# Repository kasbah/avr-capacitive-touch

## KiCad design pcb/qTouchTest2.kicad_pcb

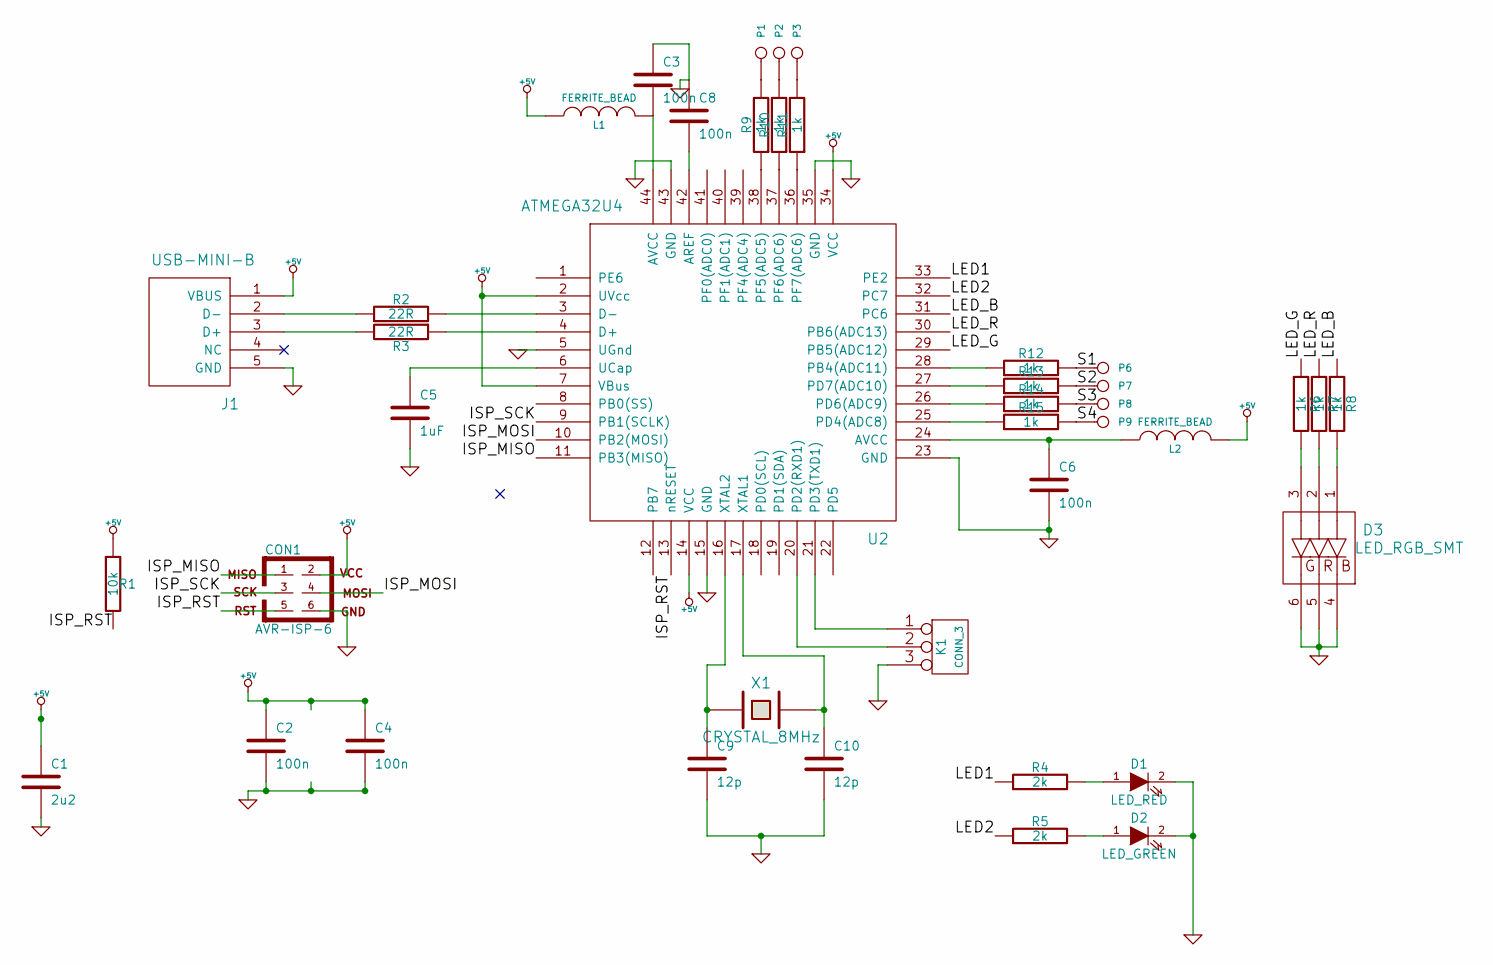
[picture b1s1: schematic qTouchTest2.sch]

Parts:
C1: 2u2
C2, C3, C4, C6, C8: 100n
C5: 1uF
C9, C10: 12p
CON1: AVR-ISP-6
D1: LED_RED
D2: LED_GREEN
D3: LED_RGB_SMT
J1: USB-MINI-B
K1: CONN_3
L1, L2: FERRITE_BEAD
P1, P2, P3, P6, P7, P8, P9: CONN_1
R1: 10k
R2, R3: 22R
R4, R5: 2k
R6, R7, R8, R9, R10, R11, R12, R13, R14, R15: 1k
U2: ATMEGA32U4
X1: CRYSTAL_8MHz

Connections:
+5V: C1.1, C2.1, C4.1, CON1.2, J1.1 (VBUS), L1.1, L2.2, R1.1, U2.2 (UVcc), U2.7 (VBus), U2.14 (VCC), U2.34 (VCC)
/ISP_MISO: CON1.1, U2.11 (PB3(MISO))
/ISP_MOSI: CON1.4, U2.10 (PB2(MOSI))
/ISP_RST: CON1.5, R1.2, U2.13 (nRESET)
/ISP_SCK: CON1.3, U2.9 (PB1(SCLK))
/LED1: R4.1, U2.33 (PE2)
/LED2: R5.1, U2.32 (PC7)
/LED_B: R8.1, U2.31 (PC6)
/LED_G: R6.1, U2.29 (PB5(ADC12))
/LED_R: R7.1, U2.30 (PB6(ADC13))
/S1: P6.1, R12.2
/S2: P7.1, R13.2
/S3: P8.1, R14.2
/S4: P9.1, R15.2
GND: C1.2, C2.2, C3.1, C4.2, C5.2, C6.2, C8.1, C9.2, C10.2, CON1.6, D1.2 (K), D2.2 (K), D3.4, D3.5, D3.6, J1.5 (GND), K1.3, U2.5 (UGnd), U2.15 (GND), U2.23 (GND), U2.35 (GND), U2.43 (GND)
unnamed: C10.1, U2.17 (XTAL1), X1.2
unnamed: C9.1, U2.16 (XTAL2), X1.1
unnamed: C5.1, U2.6 (UCap)
unnamed: R9.1, U2.38 (PF5(ADC5))
unnamed: R12.1, U2.28 (PB4(ADC11))
unnamed: R10.1, U2.37 (PF6(ADC6))
unnamed: R13.1, U2.27 (PD7(ADC10))
unnamed: R11.1, U2.36 (PF7(ADC6))
unnamed: C6.1, L2.1, U2.24 (AVCC)
unnamed: R2.2, U2.3 (D-)
unnamed: J1.2 (D-), R2.1
unnamed: J1.3 (D+), R3.2
unnamed: R3.1, U2.4 (D+)
unnamed: P3.1, R11.2
unnamed: P2.1, R10.2
unnamed: P1.1, R9.2
unnamed: D1.1 (A), R4.2
unnamed: D2.1 (A), R5.2
unnamed: C8.2, U2.42 (AREF)
unnamed: R14.1, U2.26 (PD6(ADC9))
unnamed: R15.1, U2.25 (PD4(ADC8))
unnamed: C3.2, L1.2, U2.44 (AVCC)
unnamed: K1.1, U2.21 (PD3(TXD1))
unnamed: K1.2 (PM), U2.20 (PD2(RXD1))
unnamed: D3.2, R7.2
unnamed: D3.3, R6.2
unnamed: D3.1, R8.2

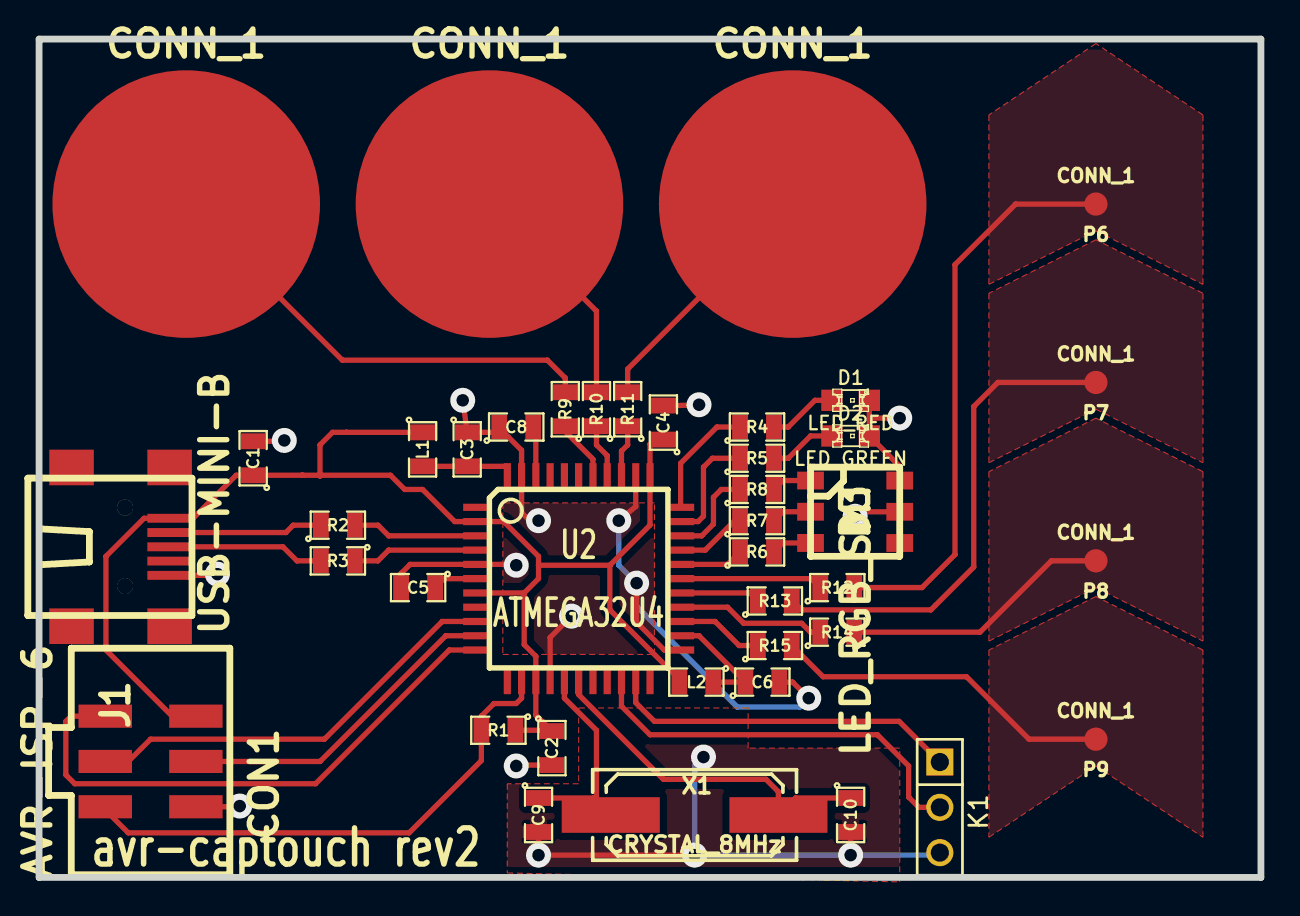
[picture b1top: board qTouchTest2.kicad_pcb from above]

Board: 2 copper layers, 68.5 x 47.0 mm, 41 parts (0 on the bottom side), 42 nets.

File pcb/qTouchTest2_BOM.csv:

"Id"	"Designator"	"Package"	"Quantity"	"Designation"	"Place on Board"	"Manufacturer"	"Manuf. No."	"Supplier"	"Supplier No."
1	"J1"	"USB-MINI-B"	1	"USB-MINI-B"	"Y"	"MOLEX"	"54819-0572"	"Farnell"	"9786473"
2	"U2"	"TQFP44"	1	"ATMEGA32U4"	"Y"	"ATMEL"	"ATMEGA32U4-AU"	"Farnell"	"1748525"
3	"CON1"	"SMT_AVR_ISP_6PIN"	1	"AVR-ISP-6"	"Y"	"FISCHER ELEKTRONIK "	" SL11 SMD 062.40S"	"Farnell"	"9729046"
4	"R1"	"SM0805"	1	"10k"	"Y"	"BOURNS"	"CR0805-JW-103ELF"	"Farnell"	"2008390"
5	"R2,R3"	"SM0805"	2	"22R"	"Y"	"YAGEO (PHYCOMP)"	"RE0805DR-0722RL"	"Farnell"	"1840604"
6	"R4,R5"	"SM0805"	2	"2k"	"Y"	"MULTICOMP"	"MCMR08X202 JT"	"Farnell"	"2073685"
7	"R6,R7,R8,R9,R10,R11,R12,R13,R14,R15"	"SM0805"	10	"1k"	"Y"	"MULTICOMP"	"MCSR08X102 JTL"	"Farnell"	"2074338"
8	"C1"	"SM0805"	1	"2u2"	"Y"	"MULTICOMP"	"MCCA00059"	"Farnell"	"1759473"
9	"C10,C9"	"SM0805"	2	"12p"	"Y"	"MULTICOMP"	"MCCA000319"	"Farnell"	"1759192"
10	"C8,C6,C4,C3,C2"	"SM0805"	5	"100n"	"Y"	"MULTICOMP"	"MCCA000274"	"Farnell"	"1759143"
11	"C5"	"SM0805"	1	"1uF"	"Y"	"MURATA"	"GRM21BF51C105ZA0"	"Farnell"	"1828851"
12	"X1"	"Q_49U3HMS"	1	"CRYSTAL_8MHz"	"Y"	"TXC"	"9C-8.000MEEJ-T"	"Farnell"	"1842347"
13	"D2"	"LED-0805"	1	"LED_GREEN"	"Y"	"KINGBRIGHT"	"KPT-2012SGC"	"Farnell"	"2099239"
14	"D1"	"LED-0805"	1	"LED_RED"	"Y"	"KINGBRIGHT"	"KPT-2012EC"	"Farnell"	"2099236"
15	"P3,P2,P1"	"CAP_BTN"	3	"CONN_1"	"N"				
16	"P9,P8,P7,P6"	"TESTPOINTx1"	4	"CONN_1"	"N"				
17	"D3"	"LED_RGB_SMT"	1	"LED_RGB_SMT"	"Y"	"CREE"	"CLV6A-FKB-CK1P1G1BB7R3R3"	"Farnell"	"1855526"
18	"L1,L2"	"SM0805"	2	"FERRITE_BEAD"	"Y"	"FAIR-RITE "	"2508051217Y0"	"Farnell"	"6347060"
19	"K1"	"PIN_ARRAY_3X1"	1	"CONN_3"	"N"

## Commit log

2013-03-27 removing private lib from project
2013-03-28 propagating C5 value change to brd and cmp
2013-03-28 updating to kicad-20130226-stable
2013-03-28 adding ferrite bead and crystal info
2013-03-28 adding colour info to LEDs
2013-03-28 adding BOM csv
2013-03-28 adding rev2 text, one trace thickness modified
    track to P6 thickness doubled as sensitivity was
    below others
2013-03-28 cleaning up output files
2013-03-28 fixing solder resist for cap touch pads
2013-03-29 reducing width of trace, moving ground plane
2013-03-30 adding ferrite bead to AVCC on pin 24
2013-03-30 propagating ferrite addition to fabrication output
2013-03-30 saving again... not sure what changed
